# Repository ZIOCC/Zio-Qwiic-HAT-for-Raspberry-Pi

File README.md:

# Zio Qwiic HAT for Raspberry Pi

> This product can be available for purchase [here](https://www.smart-prototyping.com/Zio-Qwiic-Hat-for-Raspberry-Pi).

#### Description

We will not be satisfied if you cannot use Qwiic system on Raspberry Pi in a Qwiic way, this is why we made this Qwiic Hat for Raspberry Pi. It has a standard shield design like other Raspberry Pi add-ons.

Our Qwiic Hat has eight Qwiic connectors that connect to Raspberry Pi’s I2C pins, so they all have the same I2C address.  We also add the original Pi’s ’pin names on the board for your reference.

We have two different version 2x20 female headers to offer, long pin and short pin (optional). With the long pin header, you can stack up against other Pi add-on shield. Please note that the 2x20 pin header is not pre-soldered.

#### Specification

* Board Dimension: 22.3x51.0mm
* Weight: 11.1g
* Long pins female header’s pin length: 12.2mm

#### Links

* [PCB source file and schematic](https://github.com/ZIOCC/Zio-Qwiic-HAT-for-Raspberry-Pi)

> ###### About Zio
> Zio is a new line of open sourced, compact, and grid layout boards, fully integrated for Arduino and Qwiic ecosystem. Designed ideally for wearables, robotics, small-space limitations or other on the go projects. Check out other awesome Zio products [here](https://www.smart-prototyping.com/Zio).

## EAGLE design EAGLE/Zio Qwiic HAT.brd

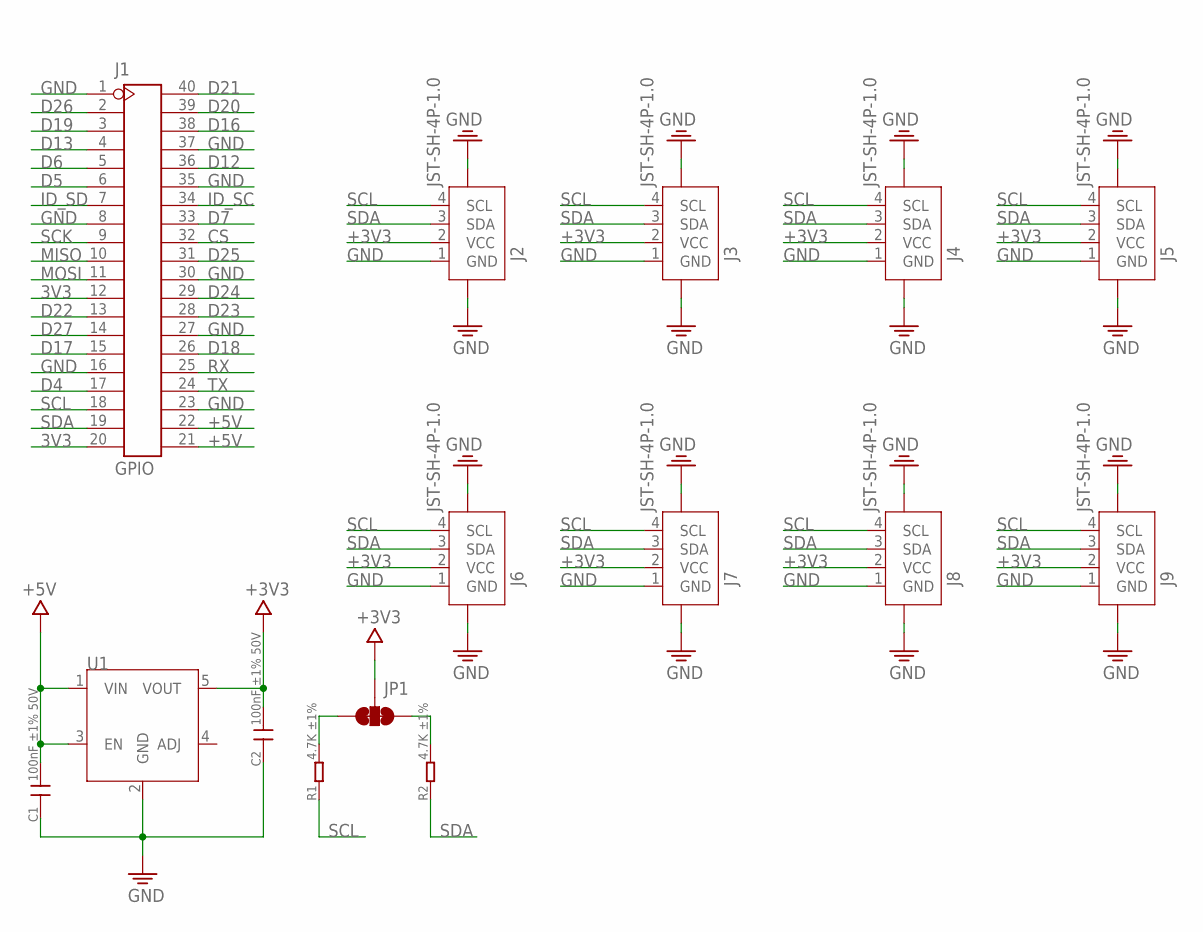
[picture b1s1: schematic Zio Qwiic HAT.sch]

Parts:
C1, C2: 100nF ±1% 50V; C0603
J1: GPIO; 2X20P_2.54
J2, J3, J4, J5, J6, J7, J8, J9: JST-SH-4P-1.0; JST-SH-4P
JP1: SMT-JUMPER_3_2-NC_TRACE
R1, R2: 4.7K ±1%; R0603
U1: AP2112; SOT23-5

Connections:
3V3: J1.12, J1.20
+3V3: C2.2, J2.2 (VCC), J3.2 (VCC), J4.2 (VCC), J5.2 (VCC), J6.2 (VCC), J7.2 (VCC), J8.2 (VCC), J9.2 (VCC), JP1.2, U1.5 (VOUT)
+5V: C1.2, J1.21, J1.22, U1.1 (VIN), U1.3 (EN)
CS: J1.32
D4: J1.17
D5: J1.6
D6: J1.5
D7: J1.33
D12: J1.36
D13: J1.4
D16: J1.38
D17: J1.15
D18: J1.26
D19: J1.3
D20: J1.39
D21: J1.40
D22: J1.13
D23: J1.28
D24: J1.29
D25: J1.31
D26: J1.2
D27: J1.14
GND: C1.1, C2.1, J1.1, J1.8, J1.16, J1.23, J1.27, J1.30, J1.35, J1.37, J2.1 (GND), J2.NC1 (5), J2.NC2 (6), J3.1 (GND), J3.NC1 (5), J3.NC2 (6), J4.1 (GND), J4.NC1 (5), J4.NC2 (6), J5.1 (GND), J5.NC1 (5), J5.NC2 (6), J6.1 (GND), J6.NC1 (5), J6.NC2 (6), J7.1 (GND), J7.NC1 (5), J7.NC2 (6), J8.1 (GND), J8.NC1 (5), J8.NC2 (6), J9.1 (GND), J9.NC1 (5), J9.NC2 (6), U1.2 (GND)
ID_SC: J1.34
ID_SD: J1.7
MISO: J1.10
MOSI: J1.11
unnamed: JP1.3, R1.2
unnamed: JP1.1, R2.2
RX: J1.25
SCK: J1.9
SCL: J1.18, J2.4 (SCL), J3.4 (SCL), J4.4 (SCL), J5.4 (SCL), J6.4 (SCL), J7.4 (SCL), J8.4 (SCL), J9.4 (SCL), R1.1
SDA: J1.19, J2.3 (SDA), J3.3 (SDA), J4.3 (SDA), J5.3 (SDA), J6.3 (SDA), J7.3 (SDA), J8.3 (SDA), J9.3 (SDA), R2.1
TX: J1.24

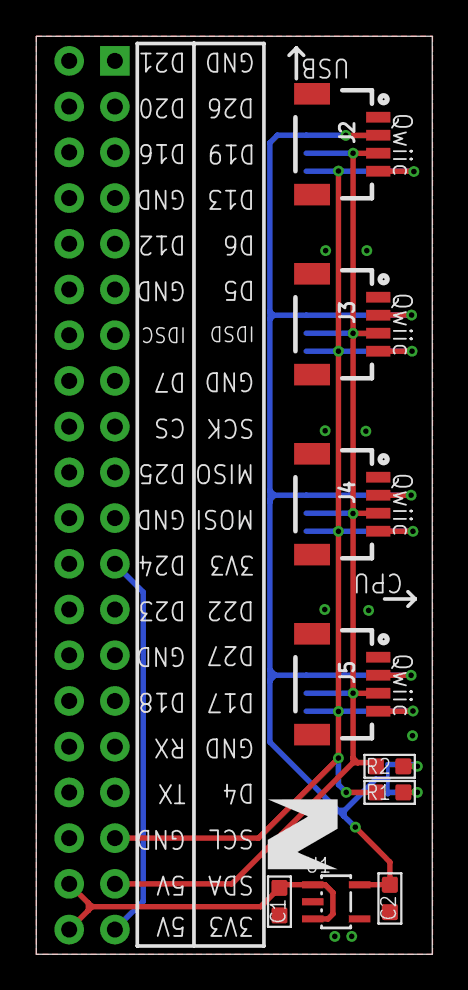
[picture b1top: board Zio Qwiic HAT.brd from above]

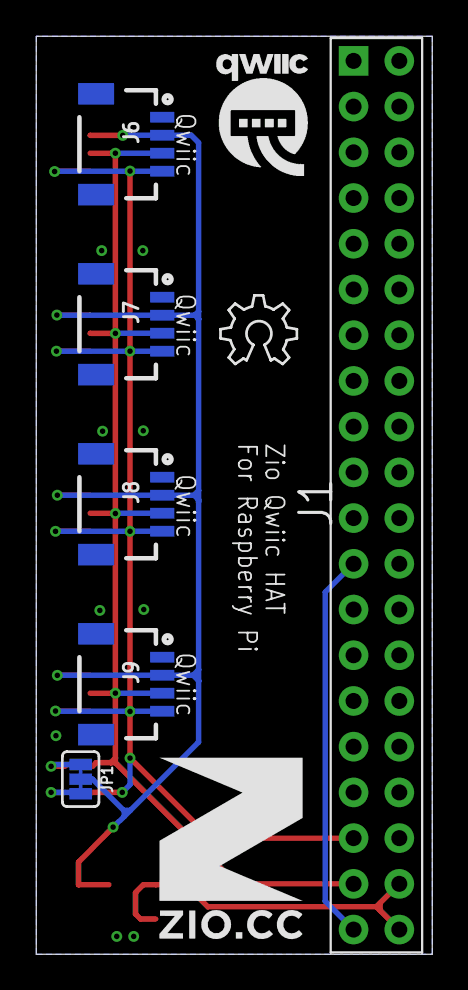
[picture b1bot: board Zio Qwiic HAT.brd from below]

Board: 2 copper layers, 22.0 x 51.0 mm, 19 parts (9 on the bottom side), 8 nets.

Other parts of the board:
U$4: 10MM
U$5: QWIIC-LOGO-MEDIUM
U$6: OSHW_6X150_NOTEXT
U$7: 6MM
